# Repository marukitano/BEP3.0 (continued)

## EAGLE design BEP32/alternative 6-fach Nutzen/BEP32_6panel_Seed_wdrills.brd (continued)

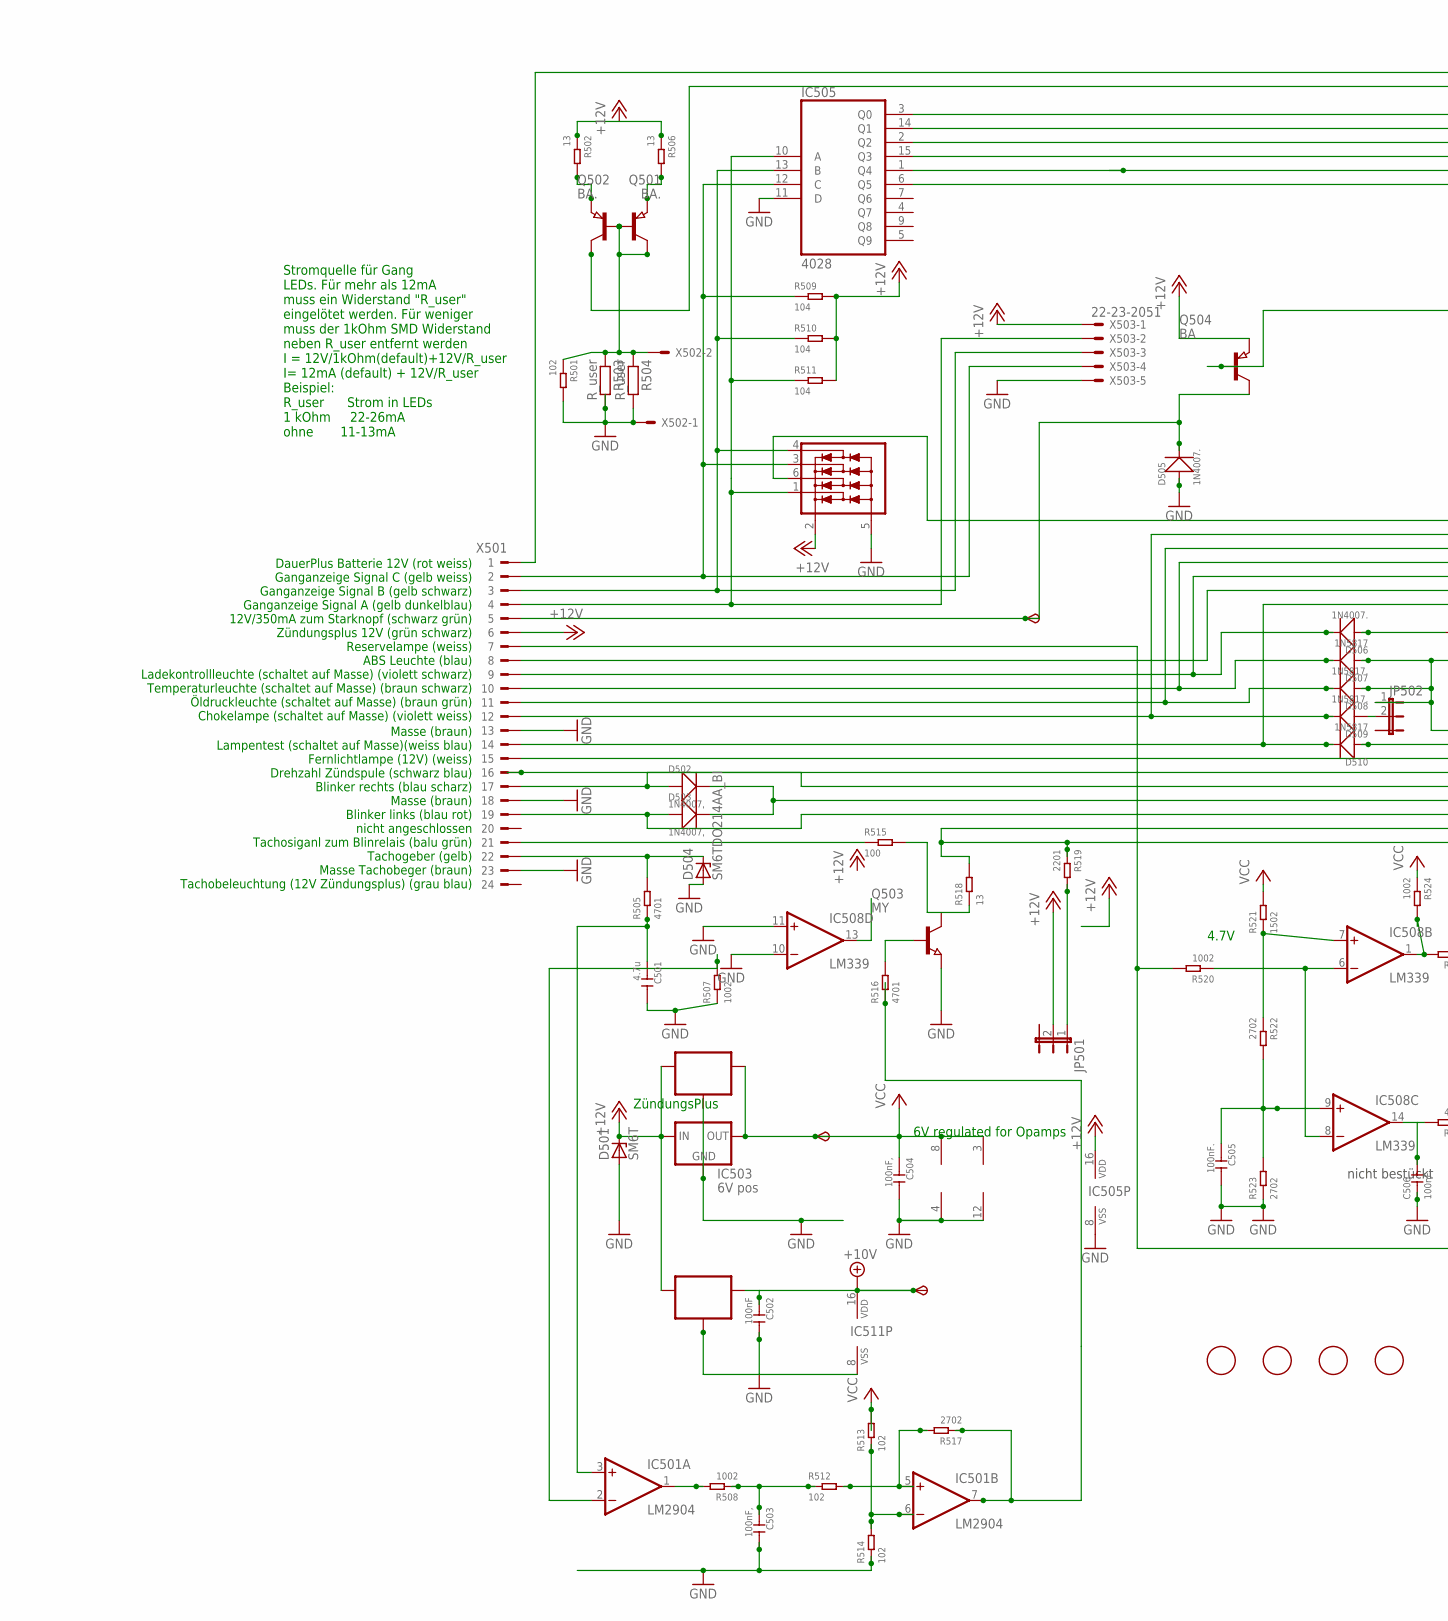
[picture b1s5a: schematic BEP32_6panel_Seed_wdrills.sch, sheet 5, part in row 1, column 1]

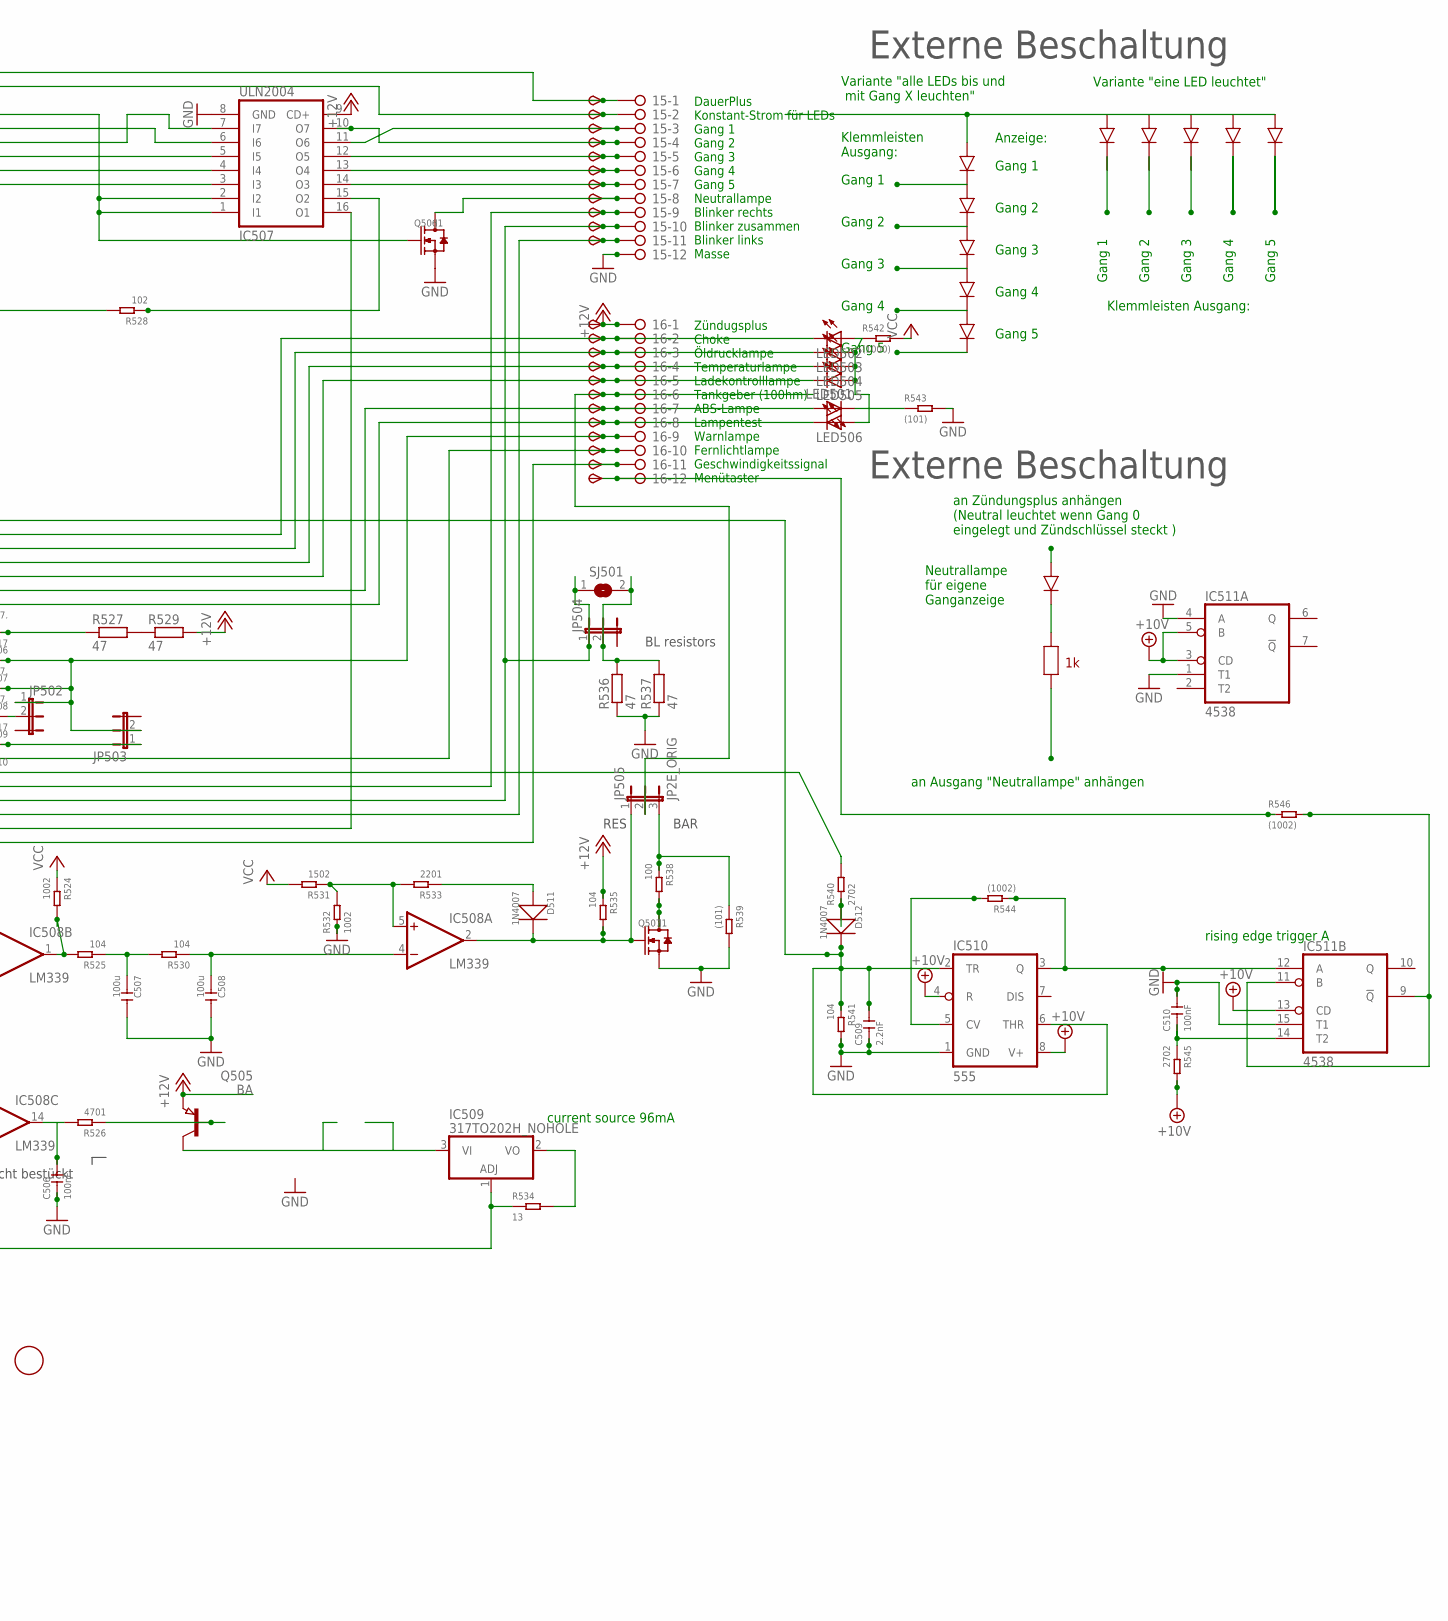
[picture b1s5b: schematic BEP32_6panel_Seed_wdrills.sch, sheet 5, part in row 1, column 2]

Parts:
6V501, 10V501: TPSB2.0; B2.0
15, 16: 2081-1132; 12-PIN
C501: 4.7u; C0805
C502, C510: 100nF; C0805
C503, C504: 100nF,; C0805
C505, C506: 100nF.; C0805
C507, C508: 100u; C1206
C509: 2.2nF; C0805
D501: SM6T; DO214AA
D502, D503: 1N4007,; DO-214AC
D504: SM6TDO214AA_BI; DO214AA_BI
D505, D506: 1N4007.; DO-214AC
D507, D510: 1N5817; DO-214AC_SLIM
D508, D509: 1N5817.; DO-214AC_SLIM
D511, D512: 1N4007; DO-214AC
FID501, FID502, FID503, FID504: FIDUCIAL; FIDUCIAL_1MM
IC501: LM2904; SO08
IC502: 78L06; SOT89_ROUND
IC503: 6V pos; 78LXX
IC504: 78L10; SOT89_ROUND
IC505: 4028; SO16
IC506: NUP4304SOT457_R; SOT457R_PHILIPS
IC507: ULN2004; SO16
IC508: LM339; SO14
IC509: 317TO202H_NOHOLE; TO220H_NOHOLE
IC510: 555; SO08
IC511: 4538; SO16
JP501, JP502, JP503, JP504: JP2EJP2_SMALLPADS; JP2_SMALLPADS
JP505: JP2E_ORIG; JP2_ORIG_SMALLPADS
LED501, LED502, LED503, LED504, LED505, LED506: LEDLD260; LD260
Q501, Q502: BA.; SOT89
Q503: MY; SOT89
Q504, Q505: BA; SOT89
Q506, Q507: J1; SOT-23
R501, R512, R513, R514, R528: 102; R0805
R502, R506, R518, R534: 13; R1206
R503, R504: R_user; R0805
R505, R516, R526: 4701; R0805
R507, R508, R520, R524, R532: 1002; R0805
R509, R510, R511, R525, R530, R535, R541: 104; R0805
R515, R538: 100; R0805
R517, R522, R523, R540, R545: 2702; R0805
R519, R533: 2201; R0805
R521, R531: 1502; R0805
R527, R529, R536, R537: 47; V235/17_1MM
R539, R543: (101); R0805
R542: (1000); R0805
R544, R546: (1002); R0805
SJ501: SJ
START501: TPSB2.0; B2.0
TP162, TP163, TP164, TP165, TP166, TP167, TP168, TP169, TP170, TP171, TP172, TP173, TP174, TP175, TP176, TP177, TP178, TP179, TP181, TP182, TP183, TP184: TPSB2.0; B2.0
TP180: TPSB1,27; B1,27
X501: CON_BMWV2; 24-PIN_V2
X502: 22-23-2021
X503: 22-23-2051

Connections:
+10V: 10V501.TP, C502.1, IC504.1 (OUT), IC510.4 (R), IC510.8 (V+), IC511.3 (CD), IC511.5 (B), IC511.13 (CD), IC511.16 (VDD), R545.2; also elsewhere on the board
+12V: 16.1, D501.C, IC502.3 (IN), IC503.IN, IC504.3 (IN), IC505.16 (VDD), IC506.2 (V+), IC507.9 (CD+), JP501.2, Q504.3 (E), Q505.3 (E), R502.1, R506.1, R509.2, R510.2, R511.2, R529.2, R535.1, TP183.TP, X501.6, X503.1; also elsewhere on the board
+12V8: IC501.7 (OUT), R516.1, R517.1
GND: 15.12, C501.2, C502.2, C503.2, C504.2, C505.2, C506.1, C507.2, C508.2, C509.1, C510.2, D501.A, D504.A, D505.1 (+), IC501.4 (V-), IC502.2 (GND), IC502.2@1 (GND), IC503.GND, IC504.2 (GND), IC504.2@1 (GND), IC505.8 (VSS), IC505.11 (D), IC506.5 (V-), IC507.8 (GND), IC508.10 (-IN), IC508.11 (+IN), IC508.12 (GND), IC510.1 (GND), IC511.1 (T1), IC511.4 (A), IC511.8 (VSS), IC511.15 (T1), Q503.3 (E), Q506.2 (S), Q507.2 (S), R501.2, R503.2, R504.2, R507.1, R514.1, R523.1, R532.1, R536.1, R537.1, R539.2, R541.2, R543.2, X501.13, X501.18, X501.23, X502.1, X503.5; also elsewhere on the board
unnamed: R527.2, R529.1
unnamed: 16.9, D507.1 (+), D508.1 (+), JP502.1, JP503.2, TP180.TP
unnamed: IC505.10 (A), IC506.1 (D1), R511.1, X501.4, X503.2
unnamed: IC505.13 (B), IC506.4 (D4), R510.1, X501.3, X503.3
unnamed: D505.2 (-), Q504.2 (C), START501.TP, X501.5
unnamed: IC505.12 (C), IC506.3 (D3), R509.1, X501.2, X503.4
unnamed: 16.7, LED501.A, TP178.TP, X501.8
unnamed: 16.2, D509.2 (-), LED502.K (C), TP173.TP, X501.12
unnamed: 16.3, D508.2 (-), LED503.K (C), TP174.TP, X501.11
unnamed: 16.4, D507.2 (-), LED504.K (C), TP175.TP, X501.10
unnamed: 16.8, D510.2 (-), LED506.K (C), TP179.TP, X501.14
unnamed: 15.9, D502.1 (+), TP170.TP, X501.17
unnamed: 15.11, D503.1 (+), TP172.TP, X501.19
unnamed: D504.C, R505.2, X501.22
unnamed: C501.1, IC501.3 (+IN), R505.1
unnamed: 16.11, IC507.16 (O1), R518.2, R519.1, TP182.TP
unnamed: IC508.1 (OUT), R524.2, R525.2
unnamed: C507.1, R525.1, R530.2
unnamed: C508.1, IC508.4 (-IN), R530.1
unnamed: IC508.5 (+IN), R531.1, R532.2, R533.2
unnamed: D511.1 (+), R533.1
unnamed: C505.1, IC508.9 (+IN), R522.2, R523.2
unnamed: C506.2, IC508.14 (OUT), R526.2
unnamed: Q505.1 (B), R526.1
unnamed: IC505.2 (Q2), IC507.7 (I7)
unnamed: 15.5, IC507.12 (O5), TP166.TP
unnamed: IC505.1 (Q4), IC507.4 (I4)
unnamed: 15.8, Q506.3 (D), TP169.TP
unnamed: 16.10, TP181.TP, X501.15
unnamed: 16.5, D506.2 (-), LED505.K (C), TP176.TP, X501.9
unnamed: D506.1 (+), R527.1
unnamed: IC505.6 (Q5), IC507.3 (I3)
unnamed: 15.4, IC507.10 (O7), TP165.TP
unnamed: IC509.1 (ADJ), R520.2, R534.1, X501.7
unnamed: IC508.6 (-IN), IC508.8 (-IN), R520.1
unnamed: 15.2, Q501.2 (C), TP163.TP
unnamed: 15.1, TP162.TP, X501.1
unnamed: R540.2, X501.16
unnamed: IC505.15 (Q3), IC507.5 (I5)
unnamed: 15.6, IC507.13 (O4), TP167.TP
unnamed: 15.7, IC507.14 (O3), TP168.TP
unnamed: 16.6, JP505.2, TP177.TP
unnamed: LED501.K (C), R543.1
unnamed: LED502.A, LED503.A, LED504.A, LED505.A, LED506.A, R542.1
unnamed: Q504.1 (B), R528.2
unnamed: IC505.3 (Q0), IC507.1 (I1), IC507.2 (I2), Q506.1 (G)
unnamed: IC505.14 (Q1), IC507.6 (I6)
unnamed: 15.3, IC507.11 (O6), TP164.TP
unnamed: Q501.1 (B), Q502.1 (B), Q502.2 (C), R501.1, R503.1, R504.1, X502.2
unnamed: Q501.3 (E), R502.2
unnamed: Q502.3 (E), R506.2
unnamed: IC508.7 (+IN), R521.1, R522.1
unnamed: IC501.2 (-IN), R507.2
unnamed: Q503.1 (B), R516.2
unnamed: Q507.3 (D), R538.2
unnamed: IC509.2 (VO), R534.2
unnamed: IC509.3 (VI), Q505.2 (C)
unnamed: C509.2, D512.2 (-), IC506.6 (D2), IC510.2 (TR), IC510.6 (THR), R541.1
unnamed: IC510.5 (CV), R544.2
unnamed: IC510.3 (Q), IC511.12 (A), R544.1
unnamed: D512.1 (+), R540.1
unnamed: 15.10, D502.2 (-), D503.2 (-), JP504.1, SJ501.1, TP171.TP
unnamed: JP504.2, R536.2, R537.2, SJ501.2
unnamed: IC511.9 (!Q), IC511.11 (B), R546.2
unnamed: C510.1, IC511.14 (T2), R545.1
unnamed: JP501.1, R519.2
unnamed: IC507.15 (O2), R528.1
unnamed: 16.12, R546.1, TP184.TP
unnamed: D509.1 (+), JP502.2
unnamed: D511.2 (-), IC508.2 (OUT), JP505.1, Q507.1 (G), R535.2
unnamed: IC501.1 (OUT), R508.2
unnamed: C503.1, R508.1, R512.1
unnamed: IC501.5 (+IN), R512.2, R517.2
unnamed: IC501.6 (-IN), R513.1, R514.2
unnamed: D510.1 (+), JP503.1
unnamed: JP505.3, R538.1, R539.1
unnamed: R515.1, X501.21
unnamed: Q503.2 (C), R515.2, R518.1
VCC: 6V501.TP, C504.1, IC501.8 (V+), IC502.1 (OUT), IC503.OUT, IC508.3 (V+), R513.2, R521.2, R524.1, R531.2, R542.2; also elsewhere on the board

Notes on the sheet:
6V regulated for Opamps
current source 96mA
ZündungsPlus
Zündugsplus Choke Öldrucklampe Temperaturlampe Ladekontrolllampe Tankgeber (100hm) ABS-Lampe Lampentest Warnlampe Fernlichtlampe Geschwindigkeitssignal Menütaster
DauerPlus Konstant-Strom für LEDs Gang 1 Gang 2 Gang 3 Gang 4 Gang 5 Neutrallampe Blinker rechts Blinker zusammen Blinker links Masse
DauerPlus Batterie 12V (rot weiss) Ganganzeige Signal C (gelb weiss) Ganganzeige Signal B (gelb schwarz) Ganganzeige Signal A (gelb dunkelblau) 12V/350mA zum Starknopf (schwarz grün) Zündungsplus 12V (grün schwarz) Reservelampe (weiss) ABS Leuchte (blau) Ladekontrollleuchte (schaltet auf Masse) (vi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
Masse (braun) Lampentest (schaltet auf Masse)(weiss blau) Fernlichtlampe (12V) (weiss) Drehzahl Zündspule (schwarz blau) Blinker rechts (blau scharz) Masse (braun) Blinker links (blau rot) nicht angeschlossen Tachosiganl zum Blinrelais (balu grün) Tachogeber (gelb) Masse Tachobeger (braun) Tachobel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
4.7V
Stromquelle für Gang LEDs. Für mehr als 12mA muss ein Widerstand "R_user" eingelötet werden. Für weniger muss der 1kOhm SMD Widerstand neben R_user entfernt werden I = 12V/1kOhm(default)+12V/R_user I= 12mA (default) + 12V/R_user Beispiel: R_user Strom in LEDs 1 kOhm 22-26mA ohne 11-13mA
Gang 1
Gang 2
Gang 3
Gang 4
Gang 5
Variante "eine LED leuchtet"
Variante "alle LEDs bis und mit Gang X leuchten"
Klemmleisten Ausgang:
Klemmleisten Ausgang:
an Zündungsplus anhängen (Neutral leuchtet wenn Gang 0 eingelegt und Zündschlüssel steckt )
an Ausgang "Neutrallampe" anhängen
Neutrallampe für eigene Ganganzeige
Externe Beschaltung
Anzeige:
nicht bestückt
rising edge trigger A
BAR
RES
BL resistors

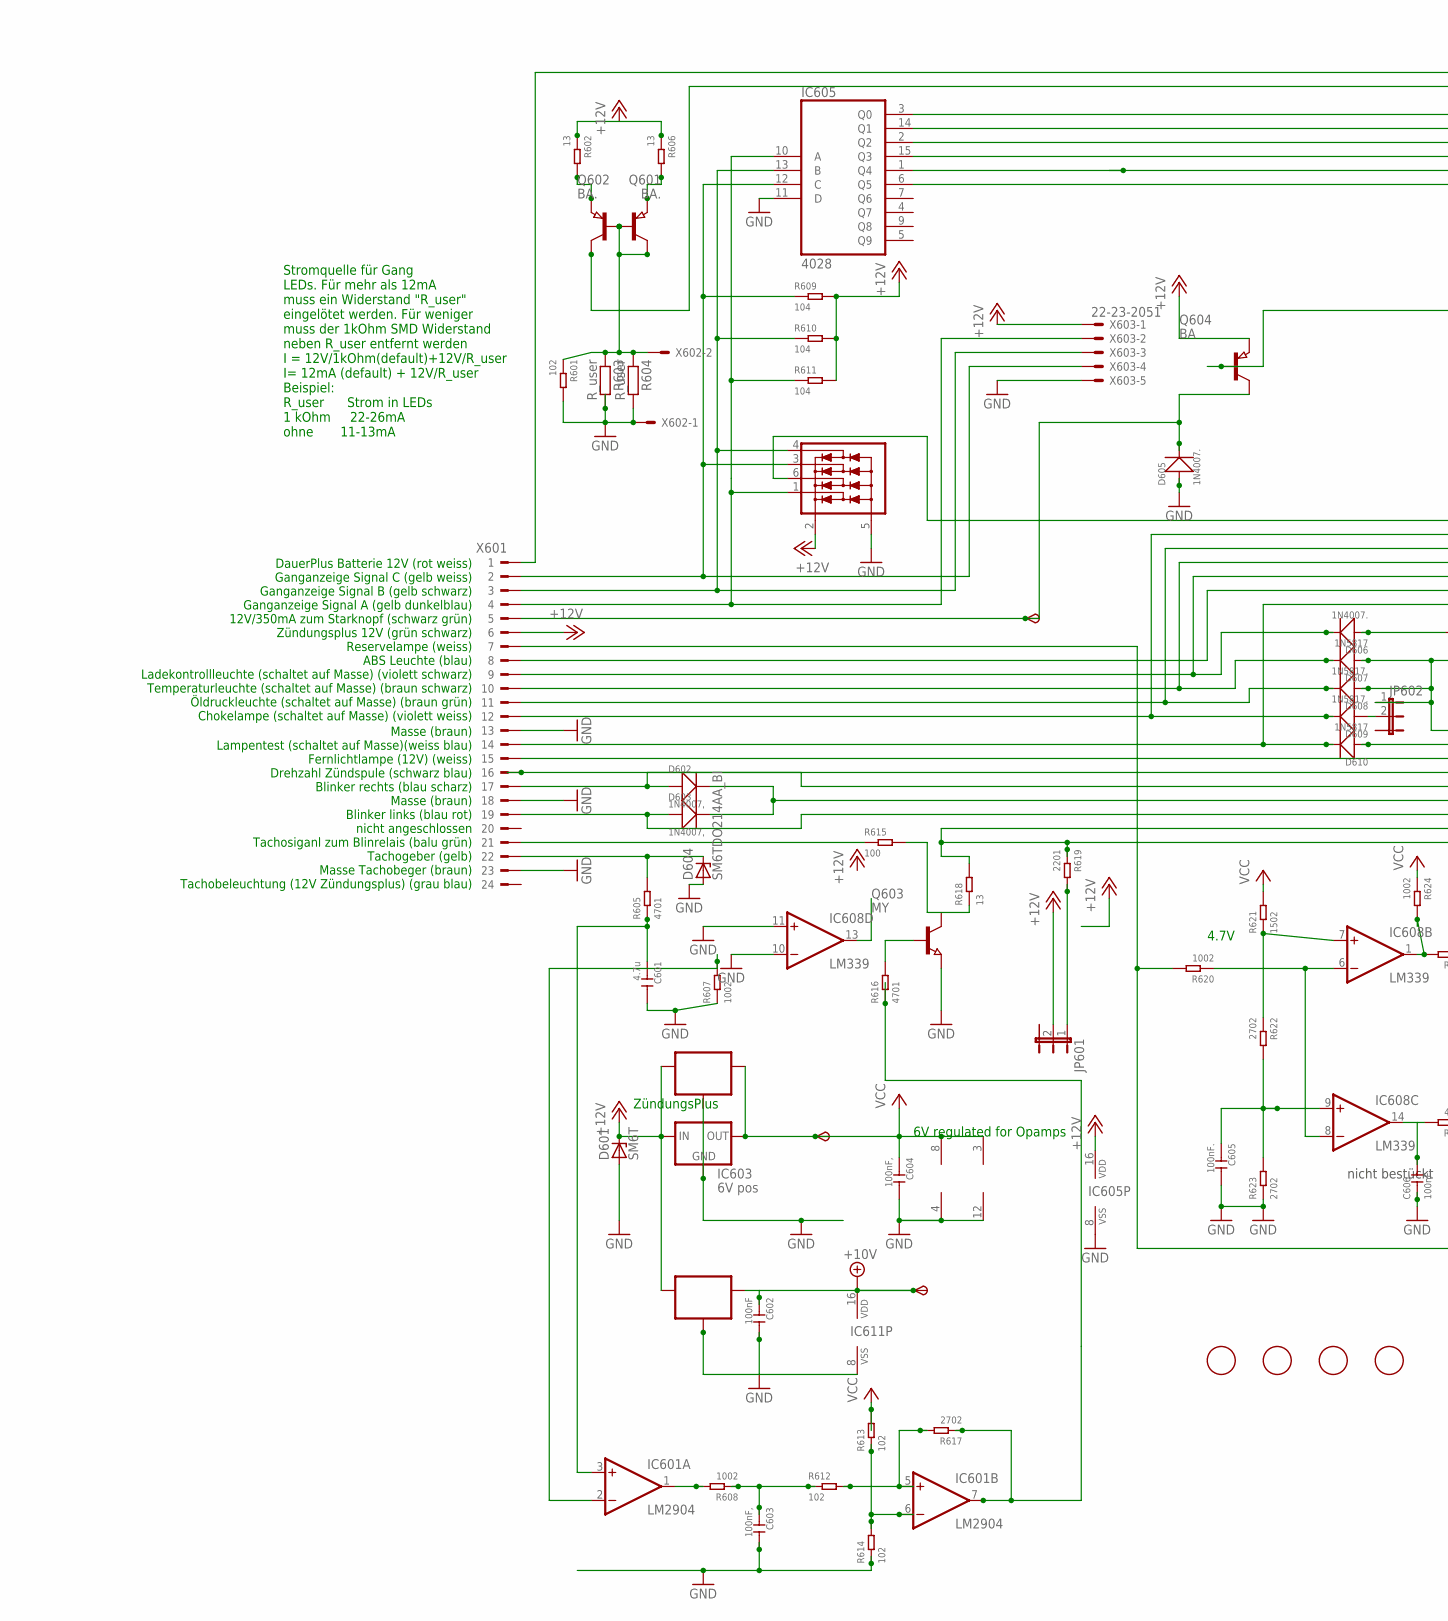
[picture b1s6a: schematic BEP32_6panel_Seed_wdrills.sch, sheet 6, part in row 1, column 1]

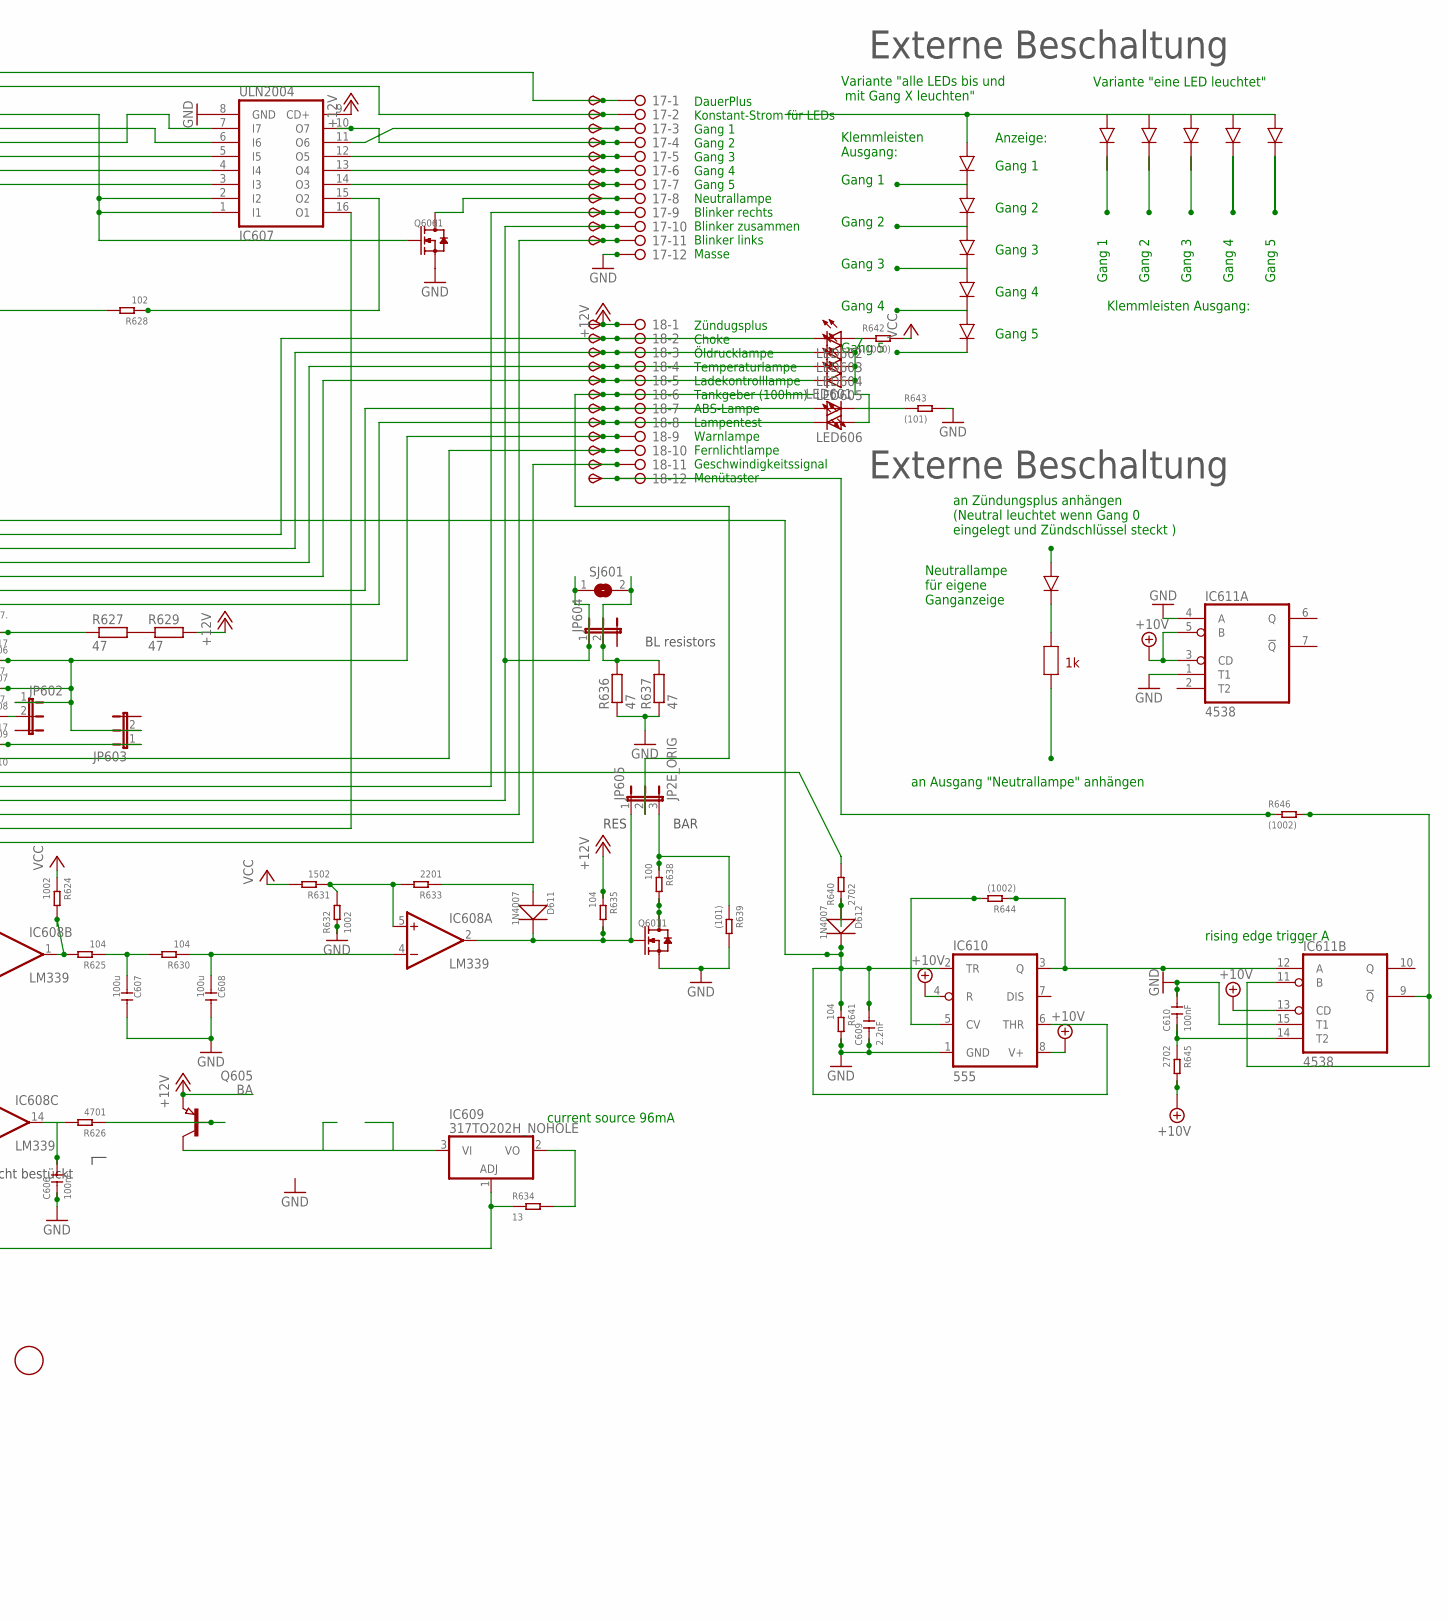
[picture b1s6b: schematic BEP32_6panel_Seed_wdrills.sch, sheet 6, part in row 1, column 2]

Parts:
6V601, 10V601: TPSB2.0; B2.0
17, 18: 2081-1132; 12-PIN
C601: 4.7u; C0805
C602, C610: 100nF; C0805
C603, C604: 100nF,; C0805
C605, C606: 100nF.; C0805
C607, C608: 100u; C1206
C609: 2.2nF; C0805
D601: SM6T; DO214AA
D602, D603: 1N4007,; DO-214AC
D604: SM6TDO214AA_BI; DO214AA_BI
D605, D606: 1N4007.; DO-214AC
D607, D610: 1N5817; DO-214AC_SLIM
D608, D609: 1N5817.; DO-214AC_SLIM
D611, D612: 1N4007; DO-214AC
FID601, FID602, FID603, FID604: FIDUCIAL; FIDUCIAL_1MM
IC601: LM2904; SO08
IC602: 78L06; SOT89_ROUND
IC603: 6V pos; 78LXX
IC604: 78L10; SOT89_ROUND
IC605: 4028; SO16
IC606: NUP4304SOT457_R; SOT457R_PHILIPS
IC607: ULN2004; SO16
IC608: LM339; SO14
IC609: 317TO202H_NOHOLE; TO220H_NOHOLE
IC610: 555; SO08
IC611: 4538; SO16
JP601, JP602, JP603, JP604: JP2EJP2_SMALLPADS; JP2_SMALLPADS
JP605: JP2E_ORIG; JP2_ORIG_SMALLPADS
LED601, LED602, LED603, LED604, LED605, LED606: LEDLD260; LD260
Q601, Q602: BA.; SOT89
Q603: MY; SOT89
Q604, Q605: BA; SOT89
Q606, Q607: J1; SOT-23
R601, R612, R613, R614, R628: 102; R0805
R602, R606, R618, R634: 13; R1206
R603, R604: R_user; R0805
R605, R616, R626: 4701; R0805
R607, R608, R620, R624, R632: 1002; R0805
R609, R610, R611, R625, R630, R635, R641: 104; R0805
R615, R638: 100; R0805
R617, R622, R623, R640, R645: 2702; R0805
R619, R633: 2201; R0805
R621, R631: 1502; R0805
R627, R629, R636, R637: 47; V235/17_1MM
R639, R643: (101); R0805
R642: (1000); R0805
R644, R646: (1002); R0805
SJ601: SJ
START601: TPSB2.0; B2.0
TP185, TP186, TP187, TP188, TP189, TP190, TP191, TP192, TP193, TP194, TP195, TP196, TP197, TP198, TP199, TP200, TP201, TP202, TP204, TP205, TP206, TP207: TPSB2.0; B2.0
TP203: TPSB1,27; B1,27
X601: CON_BMWV2; 24-PIN_V2
X602: 22-23-2021
X603: 22-23-2051

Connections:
+10V: 10V601.TP, C602.1, IC604.1 (OUT), IC610.4 (R), IC610.8 (V+), IC611.3 (CD), IC611.5 (B), IC611.13 (CD), IC611.16 (VDD), R645.2; also elsewhere on the board
+12V: 18.1, D601.C, IC602.3 (IN), IC603.IN, IC604.3 (IN), IC605.16 (VDD), IC606.2 (V+), IC607.9 (CD+), JP601.2, Q604.3 (E), Q605.3 (E), R602.1, R606.1, R609.2, R610.2, R611.2, R629.2, R635.1, TP206.TP, X601.6, X603.1; also elsewhere on the board
+12V9: IC601.7 (OUT), R616.1, R617.1
GND: 17.12, C601.2, C602.2, C603.2, C604.2, C605.2, C606.1, C607.2, C608.2, C609.1, C610.2, D601.A, D604.A, D605.1 (+), IC601.4 (V-), IC602.2 (GND), IC602.2@1 (GND), IC603.GND, IC604.2 (GND), IC604.2@1 (GND), IC605.8 (VSS), IC605.11 (D), IC606.5 (V-), IC607.8 (GND), IC608.10 (-IN), IC608.11 (+IN), IC608.12 (GND), IC610.1 (GND), IC611.1 (T1), IC611.4 (A), IC611.8 (VSS), IC611.15 (T1), Q603.3 (E), Q606.2 (S), Q607.2 (S), R601.2, R603.2, R604.2, R607.1, R614.1, R623.1, R632.1, R636.1, R637.1, R639.2, R641.2, R643.2, X601.13, X601.18, X601.23, X602.1, X603.5; also elsewhere on the board
unnamed: R627.2, R629.1
unnamed: 18.9, D607.1 (+), D608.1 (+), JP602.1, JP603.2, TP203.TP
unnamed: IC605.10 (A), IC606.1 (D1), R611.1, X601.4, X603.2
unnamed: IC605.13 (B), IC606.4 (D4), R610.1, X601.3, X603.3
unnamed: D605.2 (-), Q604.2 (C), START601.TP, X601.5
unnamed: IC605.12 (C), IC606.3 (D3), R609.1, X601.2, X603.4
unnamed: 18.7, LED601.A, TP201.TP, X601.8
unnamed: 18.2, D609.2 (-), LED602.K (C), TP196.TP, X601.12
unnamed: 18.3, D608.2 (-), LED603.K (C), TP197.TP, X601.11
unnamed: 18.4, D607.2 (-), LED604.K (C), TP198.TP, X601.10
unnamed: 18.8, D610.2 (-), LED606.K (C), TP202.TP, X601.14
unnamed: 17.9, D602.1 (+), TP193.TP, X601.17
unnamed: 17.11, D603.1 (+), TP195.TP, X601.19
unnamed: D604.C, R605.2, X601.22
unnamed: C601.1, IC601.3 (+IN), R605.1
unnamed: 18.11, IC607.16 (O1), R618.2, R619.1, TP205.TP
unnamed: IC608.1 (OUT), R624.2, R625.2
unnamed: C607.1, R625.1, R630.2
unnamed: C608.1, IC608.4 (-IN), R630.1
unnamed: IC608.5 (+IN), R631.1, R632.2, R633.2
unnamed: D611.1 (+), R633.1
unnamed: C605.1, IC608.9 (+IN), R622.2, R623.2
unnamed: C606.2, IC608.14 (OUT), R626.2
unnamed: Q605.1 (B), R626.1
unnamed: IC605.2 (Q2), IC607.7 (I7)
unnamed: 17.5, IC607.12 (O5), TP189.TP
unnamed: IC605.1 (Q4), IC607.4 (I4)
unnamed: 17.8, Q606.3 (D), TP192.TP
unnamed: 18.10, TP204.TP, X601.15
unnamed: 18.5, D606.2 (-), LED605.K (C), TP199.TP, X601.9
unnamed: D606.1 (+), R627.1
unnamed: IC605.6 (Q5), IC607.3 (I3)
unnamed: 17.4, IC607.10 (O7), TP188.TP
unnamed: IC609.1 (ADJ), R620.2, R634.1, X601.7
unnamed: IC608.6 (-IN), IC608.8 (-IN), R620.1
unnamed: 17.2, Q601.2 (C), TP186.TP
unnamed: 17.1, TP185.TP, X601.1
unnamed: R640.2, X601.16
unnamed: IC605.15 (Q3), IC607.5 (I5)
unnamed: 17.6, IC607.13 (O4), TP190.TP
unnamed: 17.7, IC607.14 (O3), TP191.TP
unnamed: 18.6, JP605.2, TP200.TP
unnamed: LED601.K (C), R643.1
unnamed: LED602.A, LED603.A, LED604.A, LED605.A, LED606.A, R642.1
unnamed: Q604.1 (B), R628.2
unnamed: IC605.3 (Q0), IC607.1 (I1), IC607.2 (I2), Q606.1 (G)
unnamed: IC605.14 (Q1), IC607.6 (I6)
unnamed: 17.3, IC607.11 (O6), TP187.TP
unnamed: Q601.1 (B), Q602.1 (B), Q602.2 (C), R601.1, R603.1, R604.1, X602.2
unnamed: Q601.3 (E), R602.2
unnamed: Q602.3 (E), R606.2
unnamed: IC608.7 (+IN), R621.1, R622.1
unnamed: IC601.2 (-IN), R607.2
unnamed: Q603.1 (B), R616.2
unnamed: Q607.3 (D), R638.2
unnamed: IC609.2 (VO), R634.2
unnamed: IC609.3 (VI), Q605.2 (C)
unnamed: C609.2, D612.2 (-), IC606.6 (D2), IC610.2 (TR), IC610.6 (THR), R641.1
unnamed: IC610.5 (CV), R644.2
unnamed: IC610.3 (Q), IC611.12 (A), R644.1
unnamed: D612.1 (+), R640.1
unnamed: 17.10, D602.2 (-), D603.2 (-), JP604.1, SJ601.1, TP194.TP
unnamed: JP604.2, R636.2, R637.2, SJ601.2
unnamed: IC611.9 (!Q), IC611.11 (B), R646.2
unnamed: C610.1, IC611.14 (T2), R645.1
unnamed: JP601.1, R619.2
unnamed: IC607.15 (O2), R628.1
unnamed: 18.12, R646.1, TP207.TP
unnamed: D609.1 (+), JP602.2
unnamed: D611.2 (-), IC608.2 (OUT), JP605.1, Q607.1 (G), R635.2
unnamed: IC601.1 (OUT), R608.2
unnamed: C603.1, R608.1, R612.1
unnamed: IC601.5 (+IN), R612.2, R617.2
unnamed: IC601.6 (-IN), R613.1, R614.2
unnamed: D610.1 (+), JP603.1
unnamed: JP605.3, R638.1, R639.1
unnamed: R615.1, X601.21
unnamed: Q603.2 (C), R615.2, R618.1
VCC: 6V601.TP, C604.1, IC601.8 (V+), IC602.1 (OUT), IC603.OUT, IC608.3 (V+), R613.2, R621.2, R624.1, R631.2, R642.2; also elsewhere on the board

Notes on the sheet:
6V regulated for Opamps
current source 96mA
ZündungsPlus
Zündugsplus Choke Öldrucklampe Temperaturlampe Ladekontrolllampe Tankgeber (100hm) ABS-Lampe Lampentest Warnlampe Fernlichtlampe Geschwindigkeitssignal Menütaster
DauerPlus Konstant-Strom für LEDs Gang 1 Gang 2 Gang 3 Gang 4 Gang 5 Neutrallampe Blinker rechts Blinker zusammen Blinker links Masse
DauerPlus Batterie 12V (rot weiss) Ganganzeige Signal C (gelb weiss) Ganganzeige Signal B (gelb schwarz) Ganganzeige Signal A (gelb dunkelblau) 12V/350mA zum Starknopf (schwarz grün) Zündungsplus 12V (grün schwarz) Reservelampe (weiss) ABS Leuchte (blau) Ladekontrollleuchte (schaltet auf Masse) (vi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
Masse (braun) Lampentest (schaltet auf Masse)(weiss blau) Fernlichtlampe (12V) (weiss) Drehzahl Zündspule (schwarz blau) Blinker rechts (blau scharz) Masse (braun) Blinker links (blau rot) nicht angeschlossen Tachosiganl zum Blinrelais (balu grün) Tachogeber (gelb) Masse Tachobeger (braun) Tachobel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
4.7V
Stromquelle für Gang LEDs. Für mehr als 12mA muss ein Widerstand "R_user" eingelötet werden. Für weniger muss der 1kOhm SMD Widerstand neben R_user entfernt werden I = 12V/1kOhm(default)+12V/R_user I= 12mA (default) + 12V/R_user Beispiel: R_user Strom in LEDs 1 kOhm 22-26mA ohne 11-13mA
Gang 1
Gang 2
Gang 3
Gang 4
Gang 5
Variante "eine LED leuchtet"
Variante "alle LEDs bis und mit Gang X leuchten"
Klemmleisten Ausgang:
Klemmleisten Ausgang:
an Zündungsplus anhängen (Neutral leuchtet wenn Gang 0 eingelegt und Zündschlüssel steckt )
an Ausgang "Neutrallampe" anhängen
Neutrallampe für eigene Ganganzeige
Externe Beschaltung
Anzeige:
nicht bestückt
rising edge trigger A
BAR
RES
BL resistors

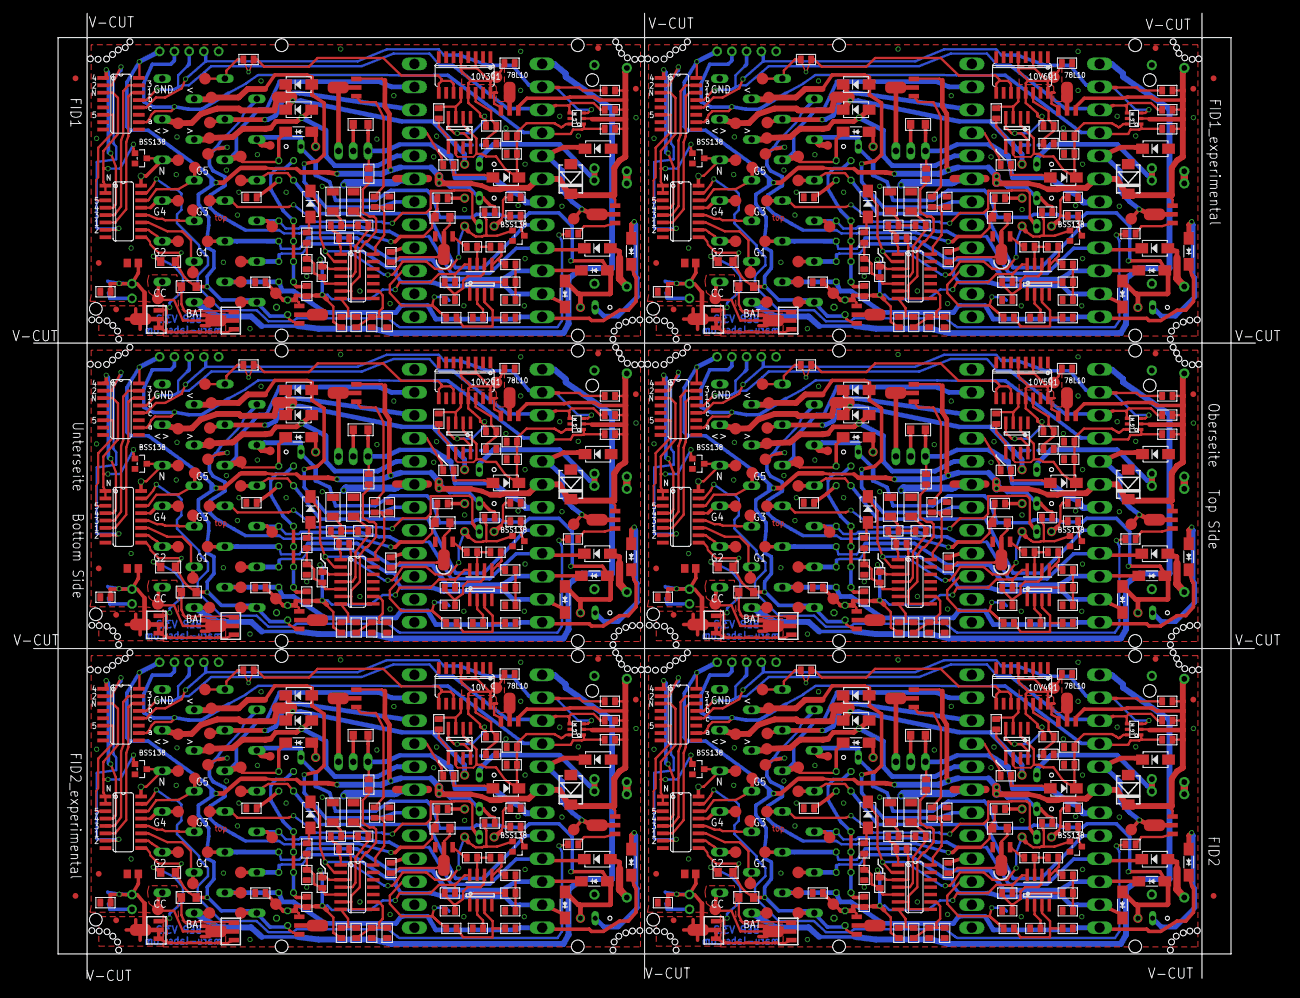
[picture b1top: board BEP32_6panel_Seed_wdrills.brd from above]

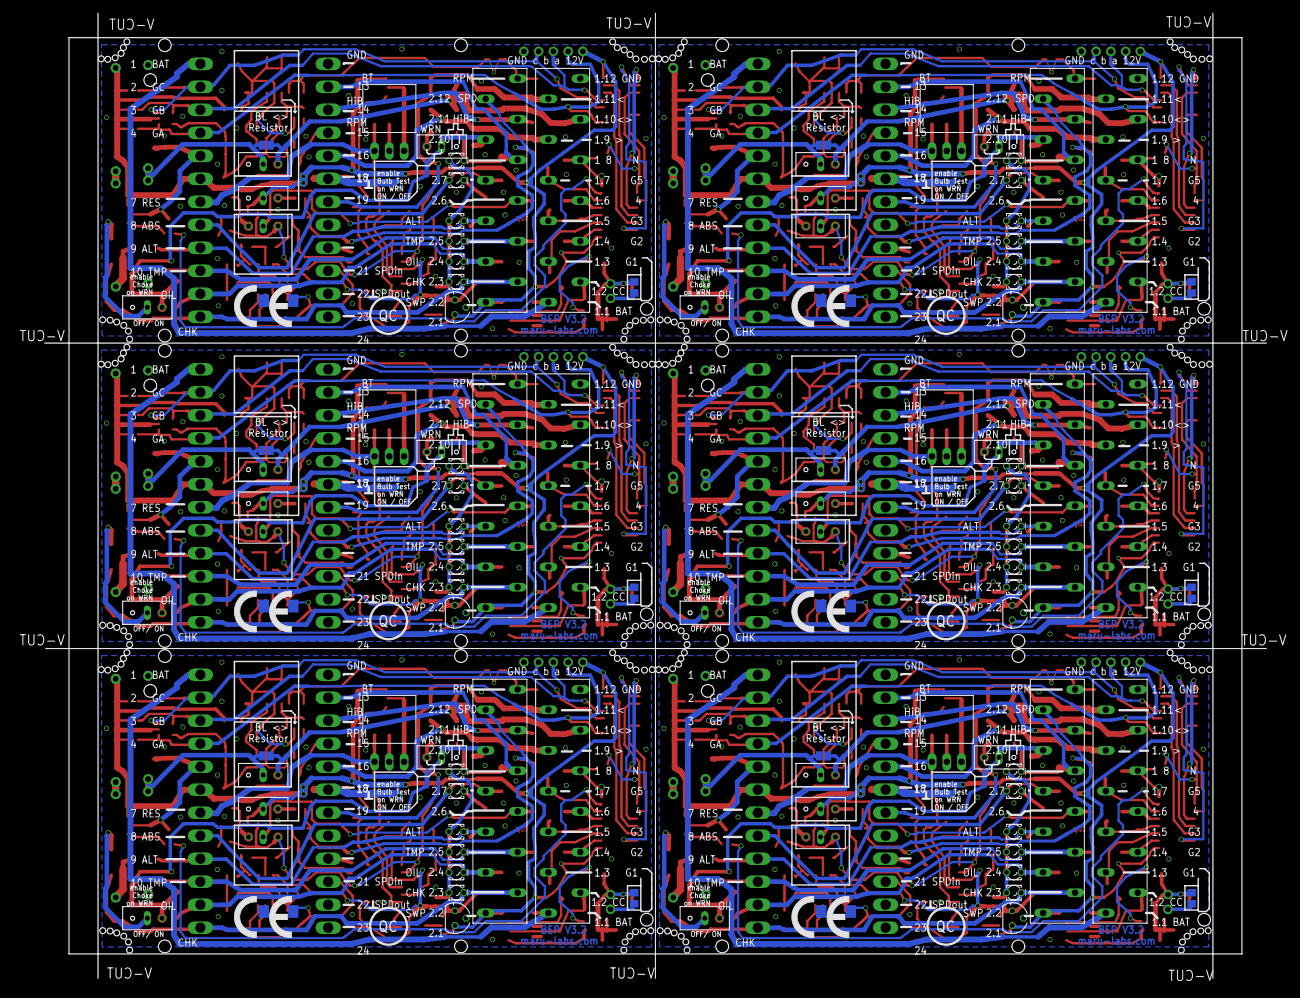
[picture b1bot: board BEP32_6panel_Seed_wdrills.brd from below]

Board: 2 copper layers, 210.4 x 166.2 mm, 808 parts (156 on the bottom side), 478 nets.

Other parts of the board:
U$1, U$2, U$3, U$7, U$8, U$9: CE_10.00

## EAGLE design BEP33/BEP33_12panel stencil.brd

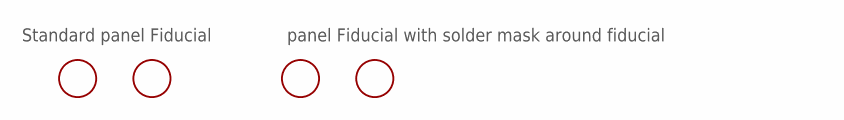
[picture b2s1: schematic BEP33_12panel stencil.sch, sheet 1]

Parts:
FID1, FID2: FIDUCIAL; FIDUCIAL_1MM
FID1B, FID2B: FIDUCIALFIDUCIAL_1MM_WITH_SOLDERMASK; FIDUCIAL_1MM_WITH_SOLDERMASK

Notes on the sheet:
Standard panel Fiducial
panel Fiducial with solder mask around fiducial
